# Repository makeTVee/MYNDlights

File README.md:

# MYNDlights

Addressable LED mod with custom 3D-printed front panels for the [Teufel MYND](https://github.com/teufelaudio/mynd-hardware) open-source Bluetooth speaker. Runs WLED on an ESP32-S3 with audio-reactive effects driven by I2S bus sniffing.

[Demo (YouTube)](https://youtube.com/shorts/J1kN-PWX2cs)

---

## How It Works

The ESP32-S3 operates as an **I2S slave**, passively sniffing the I2S data line between the MYND's Bluetooth module and its amplifier. This enables audio-reactive LED effects without any active signal interception or modification to the audio path.

WLED was recompiled with the generic I2S driver configured in slave mode to make this work.

A custom flex PCB taps the I2S connector on the mainboard — no soldering required (see [Installation](#installation)).

---

## Hardware

| Component | Details |
|-----------|---------|
| MCU | Seeed XIAO ESP32-S3 |
| LEDs | WS2812B (NeoPixel-compatible) |
| Wiring | FFC cables (6-wire flex for LED power + data) |
| Interface | Custom flex PCB + rigid carrier PCB |

---

## Variants

### Ring — 40 LEDs

### Ring — Teufel Logo

### Ring — 100 LEDs

### Matrix — 512 LEDs (32×16)

Transparent LED matrix mounted behind the speaker grille, LEDs placed between the grille holes.

CAD drawing

Installed Matrix PCB

Front with the LEDs

---

## Installation

### PCB

Custom PCBs handle I2S signal tapping and 5V power distribution for the ESP32-S3.

The flex PCB is dimensioned so its holes are slightly undersized relative to the mainboard connector. No soldering needed — press-fit and secure with the two existing screws.

The subwoofer blocks direct routing near the connector, so signals are carried via FFC cable to the upper-right corner of the enclosure.

The LED harness uses a 6-wire flex cable (2× 5V, 2× GND, 2× DATA).

> **Future work:** Low-battery LED shutoff via STM32 I2C interface.

---

## Repository Structure

```
MYNDlights/
├── CAD/      # 3D models for front panels
└── Kicad/    # PCB schematics and layout
```

---

## License

BSD 2-Clause "Simplified" License.

## References

- [Teufel MYND hardware repo](https://github.com/teufelaudio/mynd-hardware)

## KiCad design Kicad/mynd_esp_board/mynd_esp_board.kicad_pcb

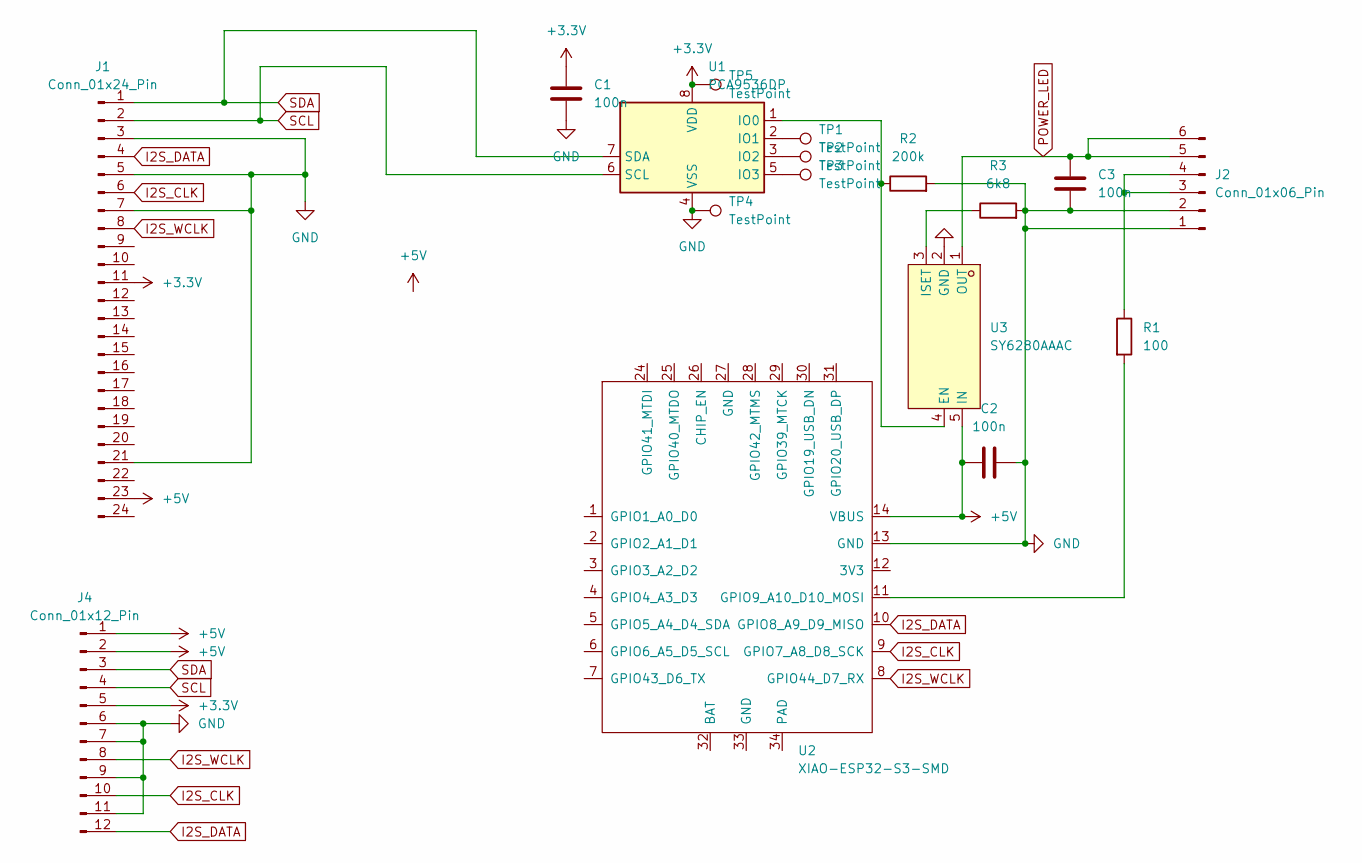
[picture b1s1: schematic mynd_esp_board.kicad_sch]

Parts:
C1, C2, C3: 100n; C_0603_1608Metric
J1: Conn_01x24_Pin
J2: Conn_01x06_Pin; FPC-SMD_F1003-ZV-06-25T-R
J4: Conn_01x12_Pin; TE_1-84953-2_1x12-1MP_P1.0mm_Horizontal
R1: 100; R_0603_1608Metric
R2: 200k; R_0603_1608Metric
R3: 6k8; R_0603_1608Metric
TP1, TP2, TP3, TP4, TP5: TestPoint; TestPoint_Pad_1.5x1.5mm
U1: PCA9536DP; TSSOP-8_3x3mm_P0.65mm
U2: XIAO-ESP32-S3-SMD
U3: SY6280AAAC; TSOT-23-5_L2.9-W1.6-P0.95-LS2.8-BL; LCSC Part C207620

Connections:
+3.3V: C1.1, J1.11, J4.5, TP5.1, U1.8 (VDD)
+5V: C2.2, J1.23, J4.1, J4.2, U2.14 (VBUS), U3.5 (IN)
GND: C1.2, C2.1, C3.2, J1.3, J1.5, J1.7, J1.21, J2.1, J2.2, J4.6, J4.7, J4.9, J4.11, R2.2, R3.2, TP4.1, U1.4 (VSS), U2.13 (GND), U3.2 (GND)
I2S_CLK: J1.6, J4.10, U2.9 (GPIO7_A8_D8_SCK)
I2S_DATA: J1.4, J4.12, U2.10 (GPIO8_A9_D9_MISO)
I2S_WCLK: J1.8, J4.8, U2.8 (GPIO44_D7_RX)
unnamed: J2.3, J2.4, R1.1
unnamed: R2.1, U1.1 (IO0), U3.4 (EN)
unnamed: TP1.1, U1.2 (IO1)
unnamed: TP2.1, U1.3 (IO2)
unnamed: TP3.1, U1.5 (IO3)
unnamed: R1.2, U2.11 (GPIO9_A10_D10_MOSI)
unnamed: R3.1, U3.3 (ISET)
POWER_LED: C3.1, J2.5, J2.6, U3.1 (OUT)
SCL: J1.2, J4.4, U1.6 (SCL)
SDA: J1.1, J4.3, U1.7 (SDA)

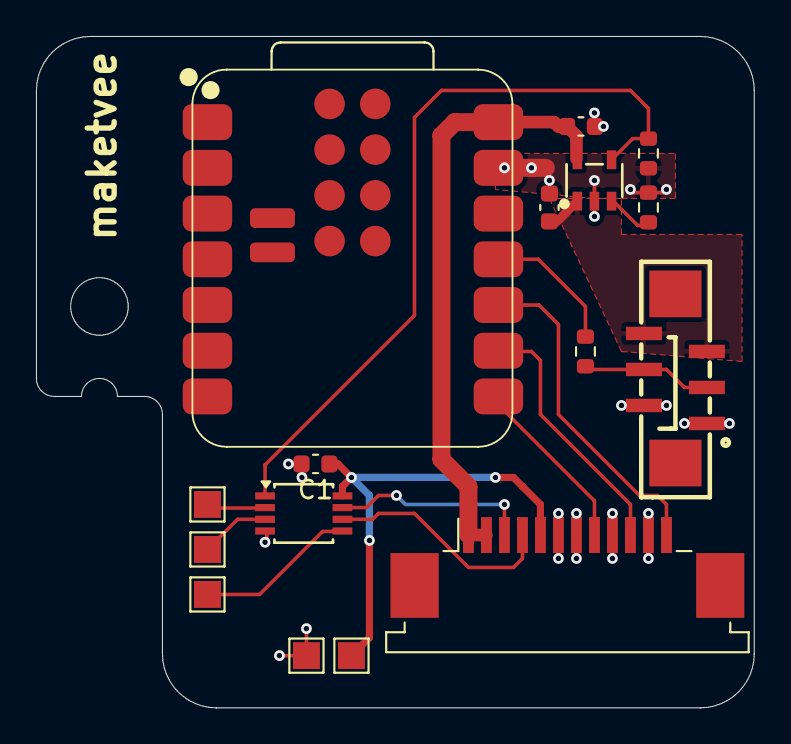
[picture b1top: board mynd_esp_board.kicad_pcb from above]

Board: 2 copper layers, 39.9 x 37.3 mm, 16 parts (0 on the bottom side), 16 nets.

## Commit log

2026-04-17 file commit
2026-04-19 Add demo video link to README
2026-04-19 Revise README for Teufel MYND and installation details
    Updated product name to 'Teufel MYND' and clarified ESP32-S3 details. Added information about custom PCBs and installation specifics.
2026-04-19 Update README with PCB installation details
    Added information about custom PCBs for I2S data and powering the ESP, along with installation details.
2026-04-19 typo fixed
2026-04-20 added matrix pictures
2026-04-20 fixed images
2026-04-20 added details
2026-04-20 Change image syntax to HTML in README.md
    Updated image syntax in README to use HTML for better control over display properties.
2026-04-20 reworked readme
2026-04-21 added cad image
2026-04-21 Update README with images of matrix components
    Added images for CAD drawing and installed matrix PCB.
2026-05-10 added 100_ring
2026-05-21 adding HdE Lightning Talk
